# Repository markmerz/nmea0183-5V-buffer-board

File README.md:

# nmea0183-5V-buffer-board

Small circuit board around 74LS244 ttl-level octal buffer chip. For working
around the interoperability issue with cheap chinese rs422-to-usb converters
which have built in 120 ohms terminating resistors. This is as spec requires,
but NASA Clipper and Cruiser series instruments are unable to wiggle the lines
with so low resistance. I tried to add resistor in series with line but that
solution turned out to be unstable.

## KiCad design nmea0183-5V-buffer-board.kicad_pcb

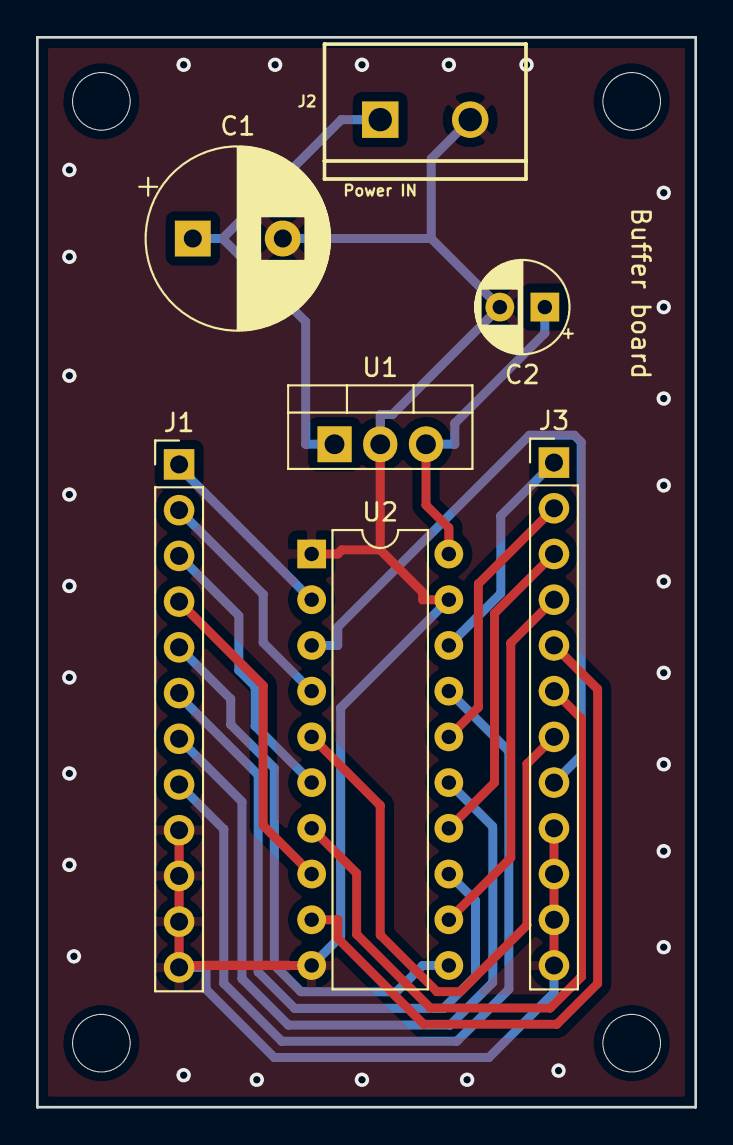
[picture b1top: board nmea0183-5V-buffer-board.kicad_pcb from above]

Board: 2 copper layers, 36.6 x 59.4 mm, 11 parts (0 on the bottom side), 19 nets.

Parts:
C1: 1000u; CP_Radial_D10.0mm_P5.00mm
C2: 1u; CP_Radial_D5.0mm_P2.50mm
H1, H2, H3, H4: MountingHole; MountingHole_3.2mm_M3
J1: Inputs; PinHeader_1x12_P2.54mm_Vertical
J2: Power IN; SCREWTERMINAL-5MM-2
J3: Outputs; PinHeader_1x12_P2.54mm_Vertical
U1: L7805; TO-220-3_Vertical
U2: 74LS244; DIP-20_W7.62mm

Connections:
+5V: C2.1, U1.3, U2.20
GND: C1.2, C2.2, J1.9, J1.10, J1.11, J1.12, J2.2, J3.9, J3.10, J3.11, J3.12, U1.2, U2.1, U2.10, U2.19
unnamed: C1.1, J2.1, U1.1
unnamed: J1.1, U2.2
unnamed: J1.2, U2.4
unnamed: J1.3, U2.6
unnamed: J1.4, U2.8
unnamed: J1.5, U2.11
unnamed: J1.6, U2.13
unnamed: J1.7, U2.15
unnamed: J1.8, U2.17
unnamed: J3.1, U2.18
unnamed: J3.2, U2.16
unnamed: J3.3, U2.14
unnamed: J3.4, U2.12
unnamed: J3.5, U2.9
unnamed: J3.6, U2.7
unnamed: J3.7, U2.5
unnamed: J3.8, U2.3

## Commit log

2021-08-21 Import.
